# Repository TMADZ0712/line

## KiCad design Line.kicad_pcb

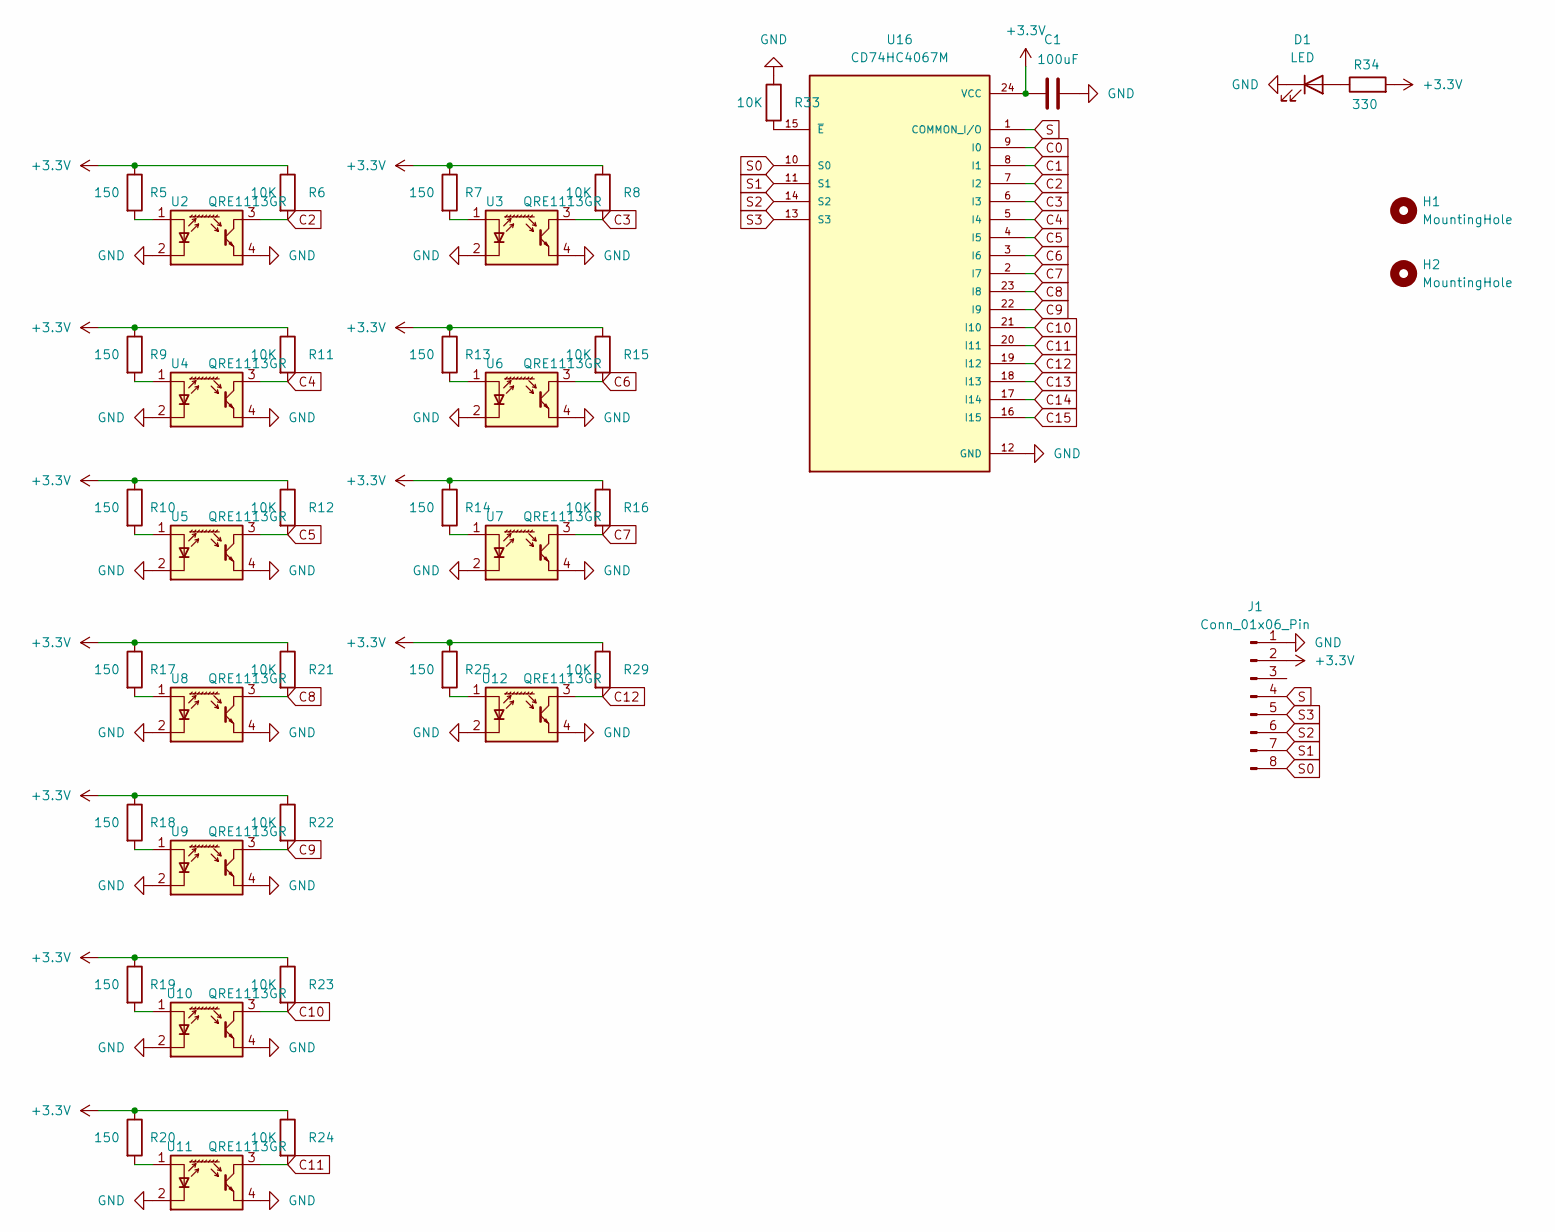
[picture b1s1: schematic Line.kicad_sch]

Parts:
C1: 100uF; C_0603_1608Metric
D1: LED; LED_0805_2012Metric
H1, H2: MountingHole; MountingHole_2.1mm
J1: Conn_01x06_Pin; PinHeader_1x08_P2.54mm_Vertical
R5, R7, R9, R10, R13, R14, R17, R18, R19, R20, R25: 150; R_0805_2012Metric
R6, R8, R11, R12, R15, R16, R21, R22, R23, R24, R29, R33: 10K; R_0805_2012Metric
R34: 330; R_0805_2012Metric
U2, U3, U4, U5, U6, U7, U8, U9, U10, U11, U12: QRE1113GR; OnSemi_CASE100CY; PARTREV 1.7
U16: CD74HC4067M; SOIC127P1030X265-24N; PARTREV D

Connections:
+3.3V: C1.1, J1.2, R5.1, R6.1, R7.1, R8.1, R9.1, R10.1, R11.1, R12.1, R13.1, R14.1, R15.1, R16.1, R17.1, R18.1, R19.1, R20.1, R21.1, R22.1, R23.1, R24.1, R25.1, R29.1, R34.2, U16.24 (VCC)
C0: U16.9 (I0)
C1: U16.8 (I1)
C2: R6.2, U2.3, U16.7 (I2)
C3: R8.2, U3.3, U16.6 (I3)
C4: R11.2, U4.3, U16.5 (I4)
C5: R12.2, U5.3, U16.4 (I5)
C6: R15.2, U6.3, U16.3 (I6)
C7: R16.2, U7.3, U16.2 (I7)
C8: R21.2, U8.3, U16.23 (I8)
C9: R22.2, U9.3, U16.22 (I9)
C10: R23.2, U10.3, U16.21 (I10)
C11: R24.2, U11.3, U16.20 (I11)
C12: R29.2, U12.3, U16.19 (I12)
C13: U16.18 (I13)
C14: U16.17 (I14)
C15: U16.16 (I15)
GND: C1.2, D1.1 (K), J1.1, R33.1, U2.2 (K), U2.4, U3.2 (K), U3.4, U4.2 (K), U4.4, U5.2 (K), U5.4, U6.2 (K), U6.4, U7.2 (K), U7.4, U8.2 (K), U8.4, U9.2 (K), U9.4, U10.2 (K), U10.4, U11.2 (K), U11.4, U12.2 (K), U12.4, U16.12 (GND)
unnamed: D1.2 (A), R34.1
unnamed: R5.2, U2.1 (A)
unnamed: R7.2, U3.1 (A)
unnamed: R9.2, U4.1 (A)
unnamed: R10.2, U5.1 (A)
unnamed: R13.2, U6.1 (A)
unnamed: R14.2, U7.1 (A)
unnamed: R17.2, U8.1 (A)
unnamed: R18.2, U9.1 (A)
unnamed: R19.2, U10.1 (A)
unnamed: R20.2, U11.1 (A)
unnamed: R25.2, U12.1 (A)
unnamed: R33.2, U16.15 (~E)
S: J1.4, U16.1 (COMMON_I/O)
S0: J1.8, U16.10 (S0)
S1: J1.7, U16.11 (S1)
S2: J1.6, U16.14 (S2)
S3: J1.5, U16.13 (S3)

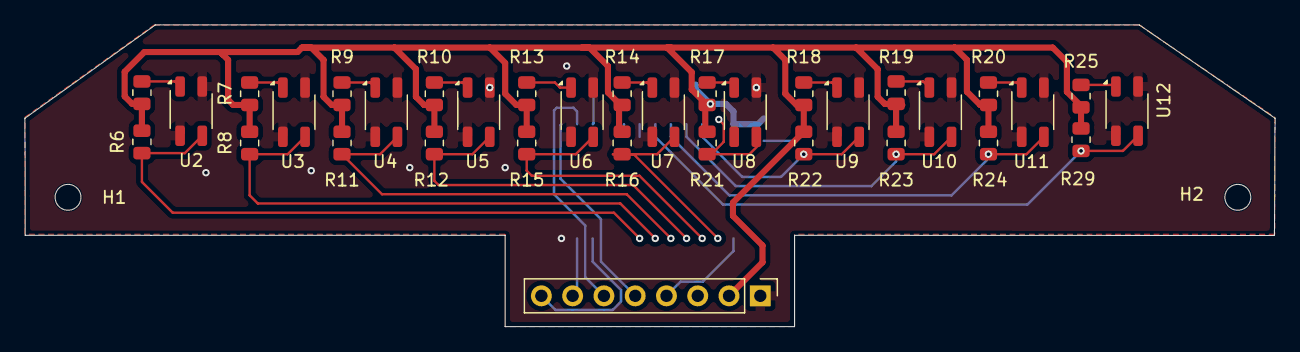
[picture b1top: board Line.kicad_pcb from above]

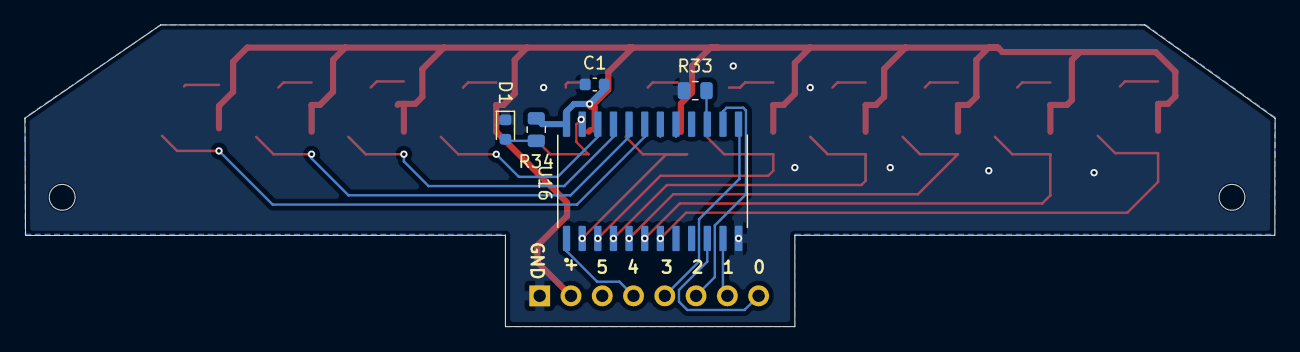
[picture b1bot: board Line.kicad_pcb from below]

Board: 2 copper layers, 101.5 x 24.5 mm, 41 parts (5 on the bottom side), 31 nets.
